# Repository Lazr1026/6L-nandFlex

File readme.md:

# 6-Layer nandFlex

NAND relocation flex for 6-Layer Wii motherboards. 

Schematic was taken from YveltalGriffin's [nandFlex](https://github.com/mackieks/nandFlex)

### Pics

### Credits
- [YveltalGriffin](https://github.com/mackieks) for the [4L nandFlex](https://github.com/mackieks/nandFlex) that I took the schematic from
- [bitbuilt.net](https://bitbuilt.net) for being cool

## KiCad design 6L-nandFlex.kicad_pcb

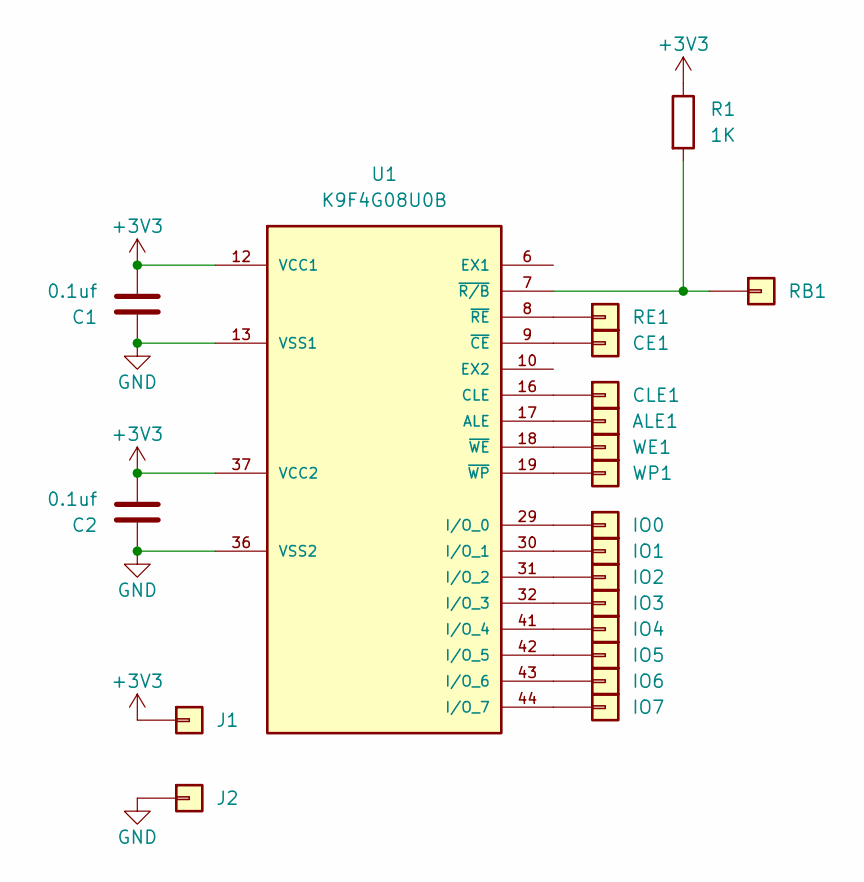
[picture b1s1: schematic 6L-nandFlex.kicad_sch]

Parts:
ALE1: Conn_01x01; wii-single-via-0.45mm
C1, C2: 0.1uf; C_0402_1005Metric
CE1: Conn_01x01; wii-single-via-0.45mm
CLE1: Conn_01x01; wii-single-via-0.45mm
IO0, IO1, IO2, IO3, IO4, IO5, IO6, IO7: Conn_01x01; wii-single-via-0.45mm
J1, J2: Conn_01x01; wii-single-via-0.45mm
R1: 1K; R_0402_1005Metric
RB1: Conn_01x01; wii-single-via-0.45mm
RE1: Conn_01x01; wii-single-via-0.45mm
U1: K9F4G08U0B; TSOP-48; MPN S34ML02G100TFI000
WE1: Conn_01x01; wii-single-via-0.45mm
WP1: Conn_01x01; wii-single-via-0.45mm

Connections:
+3V3: C1.2, C2.2, J1.1, R1.1, U1.12 (VCC1), U1.37 (VCC2)
GND: C1.1, C2.1, J2.1, U1.13 (VSS1), U1.36 (VSS2)
unnamed: ALE1.1, U1.17 (ALE)
unnamed: CE1.1, U1.9 (~CE)
unnamed: CLE1.1, U1.16 (CLE)
unnamed: IO0.1, U1.29 (I/O_0)
unnamed: IO1.1, U1.30 (I/O_1)
unnamed: IO2.1, U1.31 (I/O_2)
unnamed: IO3.1, U1.32 (I/O_3)
unnamed: IO4.1, U1.41 (I/O_4)
unnamed: IO5.1, U1.42 (I/O_5)
unnamed: IO6.1, U1.43 (I/O_6)
unnamed: IO7.1, U1.44 (I/O_7)
unnamed: R1.2, RB1.1, U1.7 (~R/B)
unnamed: RE1.1, U1.8 (~RE)
unnamed: U1.18 (~WE), WE1.1
unnamed: U1.19 (~WP), WP1.1

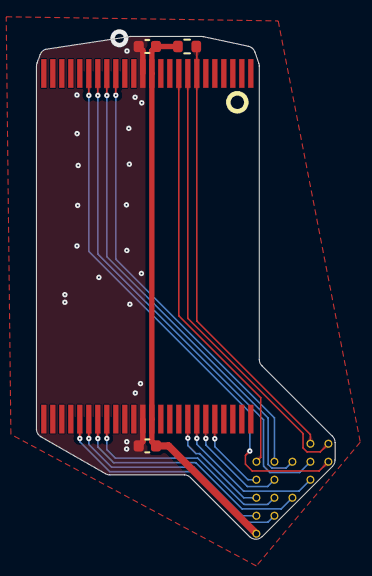
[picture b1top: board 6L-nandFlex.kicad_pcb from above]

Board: 2 copper layers, 16.6 x 27.9 mm, 20 parts (0 on the bottom side), 17 nets.

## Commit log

2025-12-07 Add pics
2025-12-07 Use .0889mm traces
2026-01-07 Add install pix
